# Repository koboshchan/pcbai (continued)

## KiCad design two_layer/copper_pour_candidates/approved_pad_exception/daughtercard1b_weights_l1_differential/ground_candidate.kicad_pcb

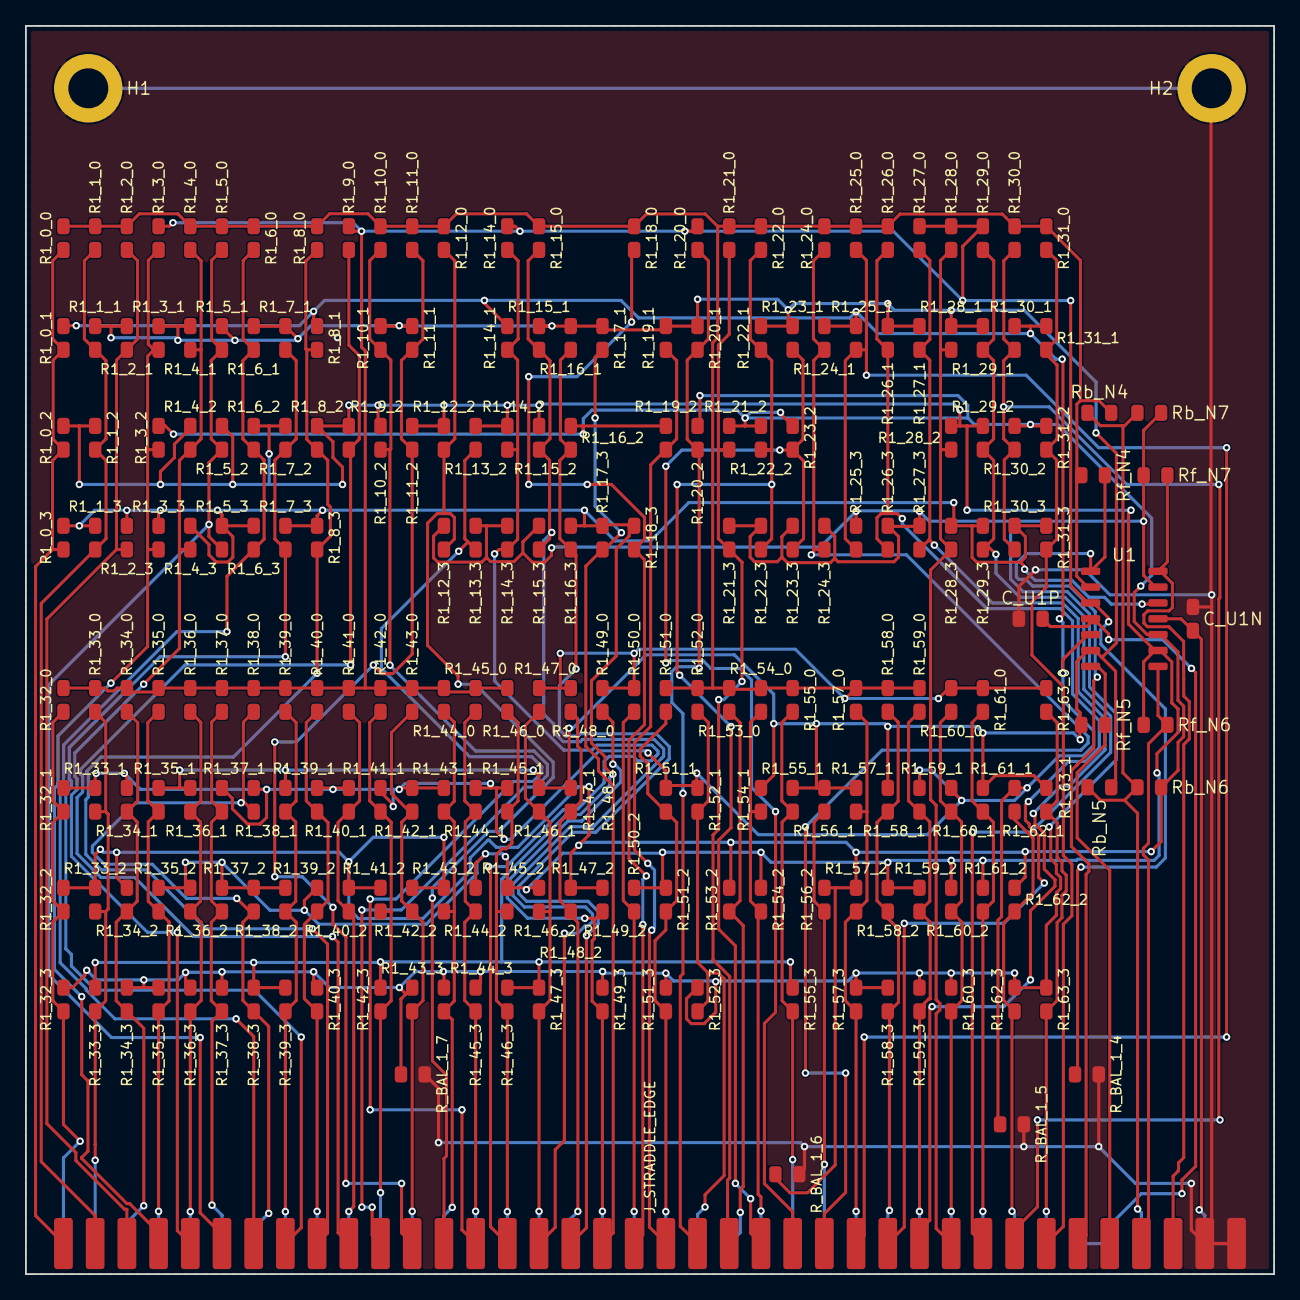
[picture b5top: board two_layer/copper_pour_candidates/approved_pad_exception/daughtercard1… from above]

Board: 2 copper layers, 100.0 x 100.0 mm, 236 parts (0 on the bottom side), 80 nets.

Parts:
C_U1N, C_U1P: 0.1uF; C_0805_2012Metric
H1, H2: MountingHole; MountingHole_3.2mm_M3_Pad
J_STRADDLE_EDGE: PinHeader_2x38_Straddle; PinHeader_2x38_Straddle_P2.54mm
R1_0_0, R1_23_2, R1_40_0, R1_41_0, R1_63_3: 51k; R_0805_2012Metric
R1_0_1, R1_5_3, R1_14_2, R1_38_0, R1_54_0: 130k; R_0805_2012Metric
R1_0_2, R1_0_3, R1_15_3, R1_21_2, R1_22_3, R1_63_1: 75k; R_0805_2012Metric
R1_1_0, R1_2_1, R1_13_2, R1_28_2, R1_35_0, R1_46_0, R1_47_2, R1_49_0, R1_51_1, R1_52_0, R1_57_0, R1_60_0, R1_60_2, R1_62_2: 200k; R_0805_2012Metric
R1_1_1, R1_3_1, R1_4_1, R1_8_3, R1_30_2, R1_36_0, R1_41_1, R1_48_1, R1_55_0: 150k; R_0805_2012Metric
R1_1_2, R1_20_0, R1_45_1, R1_45_2, R1_59_3: 240k; R_0805_2012Metric
R1_1_3, R1_23_1, R1_24_0, R1_32_1, R1_33_1, R1_48_0, R1_55_3: 91k; R_0805_2012Metric
R1_2_0, R1_29_1: 1.3M; R_0805_2012Metric
R1_2_3, R1_3_3, R1_11_0, R1_17_1, R1_18_0, R1_29_2, R1_38_1, R1_38_2, R1_39_0, R1_43_2, R1_59_0, R1_61_1: 330k; R_0805_2012Metric
R1_3_0, R1_11_2, R1_20_1, R1_30_1, R1_35_3: 430k; R_0805_2012Metric
R1_3_2, R1_22_0, R1_33_3, R1_34_2, R1_43_3, R1_46_3, R1_59_2: 680k; R_0805_2012Metric
R1_4_0, R1_9_0, R1_12_2, R1_21_3, R1_37_3, R1_58_1, R1_61_2: 270k; R_0805_2012Metric
R1_4_2, R1_4_3, R1_8_2, R1_24_3, R1_40_2, R1_40_3, R1_43_1: 110k; R_0805_2012Metric
R1_5_0, R1_14_0, R1_16_3, R1_25_3, R1_26_1, R1_42_3, R1_44_2, R1_45_3, R1_48_2, R1_49_2, R1_54_1: 510k; R_0805_2012Metric
R1_5_1, R1_11_1, R1_13_3, R1_24_1, R1_25_0, R1_29_0, R1_35_1, R1_39_1, R1_44_3, R1_45_0, R1_46_2, R1_53_2: 300k; R_0805_2012Metric
R1_5_2, R1_6_3, R1_20_2, R1_31_0, R1_32_0, R1_42_0, R1_42_1, R1_47_1, R1_47_3: 82k; R_0805_2012Metric
R1_6_0, R1_8_0, R1_31_1, R1_43_0: 100k; R_0805_2012Metric
R1_6_1, R1_10_1, R1_15_0, R1_15_1, R1_19_2, R1_27_0, R1_32_3, R1_55_1, R1_56_2, R1_57_3: 160k; R_0805_2012Metric
R1_6_2, R1_22_2: 56k; R_0805_2012Metric
R1_7_1, R1_15_2: 33k; R_0805_2012Metric
R1_7_2: 47k; R_0805_2012Metric
R1_7_3, R1_34_0, R1_35_2, R1_44_0: 390k; R_0805_2012Metric
R1_8_1, R1_22_1, R1_36_1, R1_37_0, R1_41_2, R1_42_2, R1_50_2, R1_54_2: 470k; R_0805_2012Metric
R1_9_2, R1_37_2, R1_62_1: 1M; R_0805_2012Metric
R1_10_0, R1_14_1, R1_58_2: 1.8M; R_0805_2012Metric
R1_10_2, R1_60_1: 1.6M; R_0805_2012Metric
R1_12_0, R1_21_0, R1_46_1, R1_58_3: 820k; R_0805_2012Metric
R1_12_3, R1_34_3, R1_49_3: 1.1M; R_0805_2012Metric
R1_14_3, R1_19_1, R1_25_1, R1_33_0, R1_47_0, R1_53_0: 360k; R_0805_2012Metric
R1_16_1, R1_16_2, R1_28_0, R1_28_3, R1_30_0, R1_38_3: 220k; R_0805_2012Metric
R1_17_3, R1_32_2, R1_36_2, R1_57_2, R1_60_3: 560k; R_0805_2012Metric
R1_18_3: 910k; R_0805_2012Metric
R1_23_3: 24k; R_0805_2012Metric
R1_26_0, R1_36_3, R1_52_1, R1_52_3, R1_59_1: 750k; R_0805_2012Metric
R1_26_3, R1_57_1: 1.5M; R_0805_2012Metric
R1_27_1, R1_33_2, R1_40_1, R1_51_0, R1_61_0: 120k; R_0805_2012Metric
R1_27_3, R1_51_2: 2M; R_0805_2012Metric
R1_28_1, R1_34_1, R1_44_1, R1_50_0, R1_58_0, R1_62_3: 180k; R_0805_2012Metric
R1_29_3, R1_63_0: 62k; R_0805_2012Metric
R1_30_3: 20k; R_0805_2012Metric
R1_31_2, R1_39_2: 68k; R_0805_2012Metric
R1_31_3: 43k; R_0805_2012Metric
R1_37_1: 620k; R_0805_2012Metric
R1_39_3: 27k; R_0805_2012Metric
R1_51_3: 2.2M; R_0805_2012Metric
R1_56_1: 39k; R_0805_2012Metric
R_BAL_1_4: 14.3k; R_0805_2012Metric
R_BAL_1_5: 10k; R_0805_2012Metric
R_BAL_1_6: 13k; R_0805_2012Metric
R_BAL_1_7: 16.2k; R_0805_2012Metric
Rb_N4, Rb_N5: 330k; R_0805_2012Metric
Rb_N6: 1.1M; R_0805_2012Metric
Rb_N7: 390k; R_0805_2012Metric
Rf_N4, Rf_N5, Rf_N6, Rf_N7: 100k; R_0805_2012Metric
U1: TL074; SOIC-14_3.9x8.7mm_P1.27mm

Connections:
+5V_REF: J_STRADDLE_EDGE.B35, Rb_N4.1, Rb_N5.1, Rb_N6.1, Rb_N7.1
+15V: C_U1P.2, J_STRADDLE_EDGE.B33, J_STRADDLE_EDGE.B34, U1.4
-15V: C_U1N.1, J_STRADDLE_EDGE.B37, J_STRADDLE_EDGE.B38, U1.11
GND: C_U1N.2, C_U1P.1, H1.1, H2.1, J_STRADDLE_EDGE.A37, J_STRADDLE_EDGE.A38, R_BAL_1_4.2, R_BAL_1_5.2, R_BAL_1_6.2, R_BAL_1_7.2
INV_N4: R1_0_0.2, R1_1_0.2, R1_2_0.2, R1_4_0.2, R1_5_0.2, R1_6_0.2, R1_8_0.2, R1_10_0.2, R1_11_0.2, R1_12_0.2, R1_15_0.2, R1_18_0.2, R1_21_0.2, R1_22_0.2, R1_24_0.2, R1_25_0.2, R1_26_0.2, R1_30_0.2, R1_31_0.2, R1_47_0.2, R1_48_0.2, R1_49_0.2, R1_50_0.2, R1_51_0.2, R1_52_0.2, R1_53_0.2, R1_54_0.2, R1_55_0.2, R1_57_0.2, R1_58_0.2, R1_59_0.2, R1_60_0.2, R1_61_0.2, R1_63_0.2, Rb_N4.2, Rf_N4.1, U1.2
INV_N5: R1_1_1.2, R1_2_1.2, R1_3_1.2, R1_4_1.2, R1_5_1.2, R1_6_1.2, R1_7_1.2, R1_10_1.2, R1_11_1.2, R1_15_1.2, R1_16_1.2, R1_17_1.2, R1_19_1.2, R1_20_1.2, R1_22_1.2, R1_23_1.2, R1_26_1.2, R1_27_1.2, R1_28_1.2, R1_29_1.2, R1_35_1.2, R1_36_1.2, R1_39_1.2, R1_47_1.2, R1_48_1.2, R1_54_1.2, R1_55_1.2, R1_56_1.2, R1_57_1.2, R1_58_1.2, R1_61_1.2, R1_63_1.2, Rb_N5.2, Rf_N5.1, U1.6
INV_N6: R1_0_2.2, R1_1_2.2, R1_4_2.2, R1_5_2.2, R1_6_2.2, R1_7_2.2, R1_8_2.2, R1_9_2.2, R1_10_2.2, R1_11_2.2, R1_12_2.2, R1_13_2.2, R1_14_2.2, R1_15_2.2, R1_28_2.2, R1_29_2.2, R1_35_2.2, R1_36_2.2, R1_37_2.2, R1_38_2.2, R1_39_2.2, R1_40_2.2, R1_45_2.2, R1_46_2.2, R1_47_2.2, R1_50_2.2, R1_51_2.2, R1_54_2.2, R1_58_2.2, R1_59_2.2, R1_60_2.2, R1_61_2.2, Rf_N6.1, U1.9
INV_N7: R1_12_3.2, R1_13_3.2, R1_14_3.2, R1_15_3.2, R1_21_3.2, R1_22_3.2, R1_23_3.2, R1_24_3.2, R1_25_3.2, R1_26_3.2, R1_27_3.2, R1_32_3.2, R1_34_3.2, R1_35_3.2, R1_36_3.2, R1_37_3.2, R1_40_3.2, R1_43_3.2, R1_44_3.2, R1_45_3.2, R1_49_3.2, R1_51_3.2, R1_52_3.2, R1_57_3.2, R1_58_3.2, R1_59_3.2, R1_60_3.2, R1_62_3.2, R1_63_3.2, R_BAL_1_7.1, Rb_N7.2, Rf_N7.1, U1.13
IN_0: J_STRADDLE_EDGE.A1, R1_0_0.1, R1_0_1.1, R1_0_2.1, R1_0_3.1
IN_1: J_STRADDLE_EDGE.A2, R1_1_0.1, R1_1_1.1, R1_1_2.1, R1_1_3.1
IN_2: J_STRADDLE_EDGE.A3, R1_2_0.1, R1_2_1.1, R1_2_3.1
IN_3: J_STRADDLE_EDGE.A4, R1_3_0.1, R1_3_1.1, R1_3_2.1, R1_3_3.1
IN_4: J_STRADDLE_EDGE.A5, R1_4_0.1, R1_4_1.1, R1_4_2.1, R1_4_3.1
IN_5: J_STRADDLE_EDGE.A6, R1_5_0.1, R1_5_1.1, R1_5_2.1, R1_5_3.1
IN_6: J_STRADDLE_EDGE.A7, R1_6_0.1, R1_6_1.1, R1_6_2.1, R1_6_3.1
IN_7: J_STRADDLE_EDGE.A8, R1_7_1.1, R1_7_2.1, R1_7_3.1
IN_8: J_STRADDLE_EDGE.A9, R1_8_0.1, R1_8_1.1, R1_8_2.1, R1_8_3.1
IN_9: J_STRADDLE_EDGE.A10, R1_9_0.1, R1_9_2.1
IN_10: J_STRADDLE_EDGE.A11, R1_10_0.1, R1_10_1.1, R1_10_2.1
IN_11: J_STRADDLE_EDGE.A12, R1_11_0.1, R1_11_1.1, R1_11_2.1
IN_12: J_STRADDLE_EDGE.A13, R1_12_0.1, R1_12_2.1, R1_12_3.1
IN_13: J_STRADDLE_EDGE.A14, R1_13_2.1, R1_13_3.1
IN_14: J_STRADDLE_EDGE.A15, R1_14_0.1, R1_14_1.1, R1_14_2.1, R1_14_3.1
IN_15: J_STRADDLE_EDGE.A16, R1_15_0.1, R1_15_1.1, R1_15_2.1, R1_15_3.1
IN_16: J_STRADDLE_EDGE.A17, R1_16_1.1, R1_16_2.1, R1_16_3.1
IN_17: J_STRADDLE_EDGE.A18, R1_17_1.1, R1_17_3.1
IN_18: J_STRADDLE_EDGE.A19, R1_18_0.1, R1_18_3.1
IN_19: J_STRADDLE_EDGE.A20, R1_19_1.1, R1_19_2.1
IN_20: J_STRADDLE_EDGE.A21, R1_20_0.1, R1_20_1.1, R1_20_2.1
IN_21: J_STRADDLE_EDGE.A22, R1_21_0.1, R1_21_2.1, R1_21_3.1
IN_22: J_STRADDLE_EDGE.A23, R1_22_0.1, R1_22_1.1, R1_22_2.1, R1_22_3.1
IN_23: J_STRADDLE_EDGE.A24, R1_23_1.1, R1_23_2.1, R1_23_3.1
IN_24: J_STRADDLE_EDGE.A25, R1_24_0.1, R1_24_1.1, R1_24_3.1
IN_25: J_STRADDLE_EDGE.A26, R1_25_0.1, R1_25_1.1, R1_25_3.1
IN_26: J_STRADDLE_EDGE.A27, R1_26_0.1, R1_26_1.1, R1_26_3.1
IN_27: J_STRADDLE_EDGE.A28, R1_27_0.1, R1_27_1.1, R1_27_3.1
IN_28: J_STRADDLE_EDGE.A29, R1_28_0.1, R1_28_1.1, R1_28_2.1, R1_28_3.1
IN_29: J_STRADDLE_EDGE.A30, R1_29_0.1, R1_29_1.1, R1_29_2.1, R1_29_3.1
IN_30: J_STRADDLE_EDGE.A31, R1_30_0.1, R1_30_1.1, R1_30_2.1, R1_30_3.1
IN_31: J_STRADDLE_EDGE.A32, R1_31_0.1, R1_31_1.1, R1_31_2.1, R1_31_3.1
IN_32: J_STRADDLE_EDGE.B1, R1_32_0.1, R1_32_1.1, R1_32_2.1, R1_32_3.1
IN_33: J_STRADDLE_EDGE.B2, R1_33_0.1, R1_33_1.1, R1_33_2.1, R1_33_3.1
IN_34: J_STRADDLE_EDGE.B3, R1_34_0.1, R1_34_1.1, R1_34_2.1, R1_34_3.1
IN_35: J_STRADDLE_EDGE.B4, R1_35_0.1, R1_35_1.1, R1_35_2.1, R1_35_3.1
IN_36: J_STRADDLE_EDGE.B5, R1_36_0.1, R1_36_1.1, R1_36_2.1, R1_36_3.1
IN_37: J_STRADDLE_EDGE.B6, R1_37_0.1, R1_37_1.1, R1_37_2.1, R1_37_3.1
IN_38: J_STRADDLE_EDGE.B7, R1_38_0.1, R1_38_1.1, R1_38_2.1, R1_38_3.1
IN_39: J_STRADDLE_EDGE.B8, R1_39_0.1, R1_39_1.1, R1_39_2.1, R1_39_3.1
IN_40: J_STRADDLE_EDGE.B9, R1_40_0.1, R1_40_1.1, R1_40_2.1, R1_40_3.1
IN_41: J_STRADDLE_EDGE.B10, R1_41_0.1, R1_41_1.1, R1_41_2.1
IN_42: J_STRADDLE_EDGE.B11, R1_42_0.1, R1_42_1.1, R1_42_2.1, R1_42_3.1
IN_43: J_STRADDLE_EDGE.B12, R1_43_0.1, R1_43_1.1, R1_43_2.1, R1_43_3.1
IN_44: J_STRADDLE_EDGE.B13, R1_44_0.1, R1_44_1.1, R1_44_2.1, R1_44_3.1
IN_45: J_STRADDLE_EDGE.B14, R1_45_0.1, R1_45_1.1, R1_45_2.1, R1_45_3.1
IN_46: J_STRADDLE_EDGE.B15, R1_46_0.1, R1_46_1.1, R1_46_2.1, R1_46_3.1
IN_47: J_STRADDLE_EDGE.B16, R1_47_0.1, R1_47_1.1, R1_47_2.1, R1_47_3.1
IN_48: J_STRADDLE_EDGE.B17, R1_48_0.1, R1_48_1.1, R1_48_2.1
IN_49: J_STRADDLE_EDGE.B18, R1_49_0.1, R1_49_2.1, R1_49_3.1
IN_50: J_STRADDLE_EDGE.B19, R1_50_0.1, R1_50_2.1
IN_51: J_STRADDLE_EDGE.B20, R1_51_0.1, R1_51_1.1, R1_51_2.1, R1_51_3.1
IN_52: J_STRADDLE_EDGE.B21, R1_52_0.1, R1_52_1.1, R1_52_3.1
IN_53: J_STRADDLE_EDGE.B22, R1_53_0.1, R1_53_2.1
IN_54: J_STRADDLE_EDGE.B23, R1_54_0.1, R1_54_1.1, R1_54_2.1
IN_55: J_STRADDLE_EDGE.B24, R1_55_0.1, R1_55_1.1, R1_55_3.1
IN_56: J_STRADDLE_EDGE.B25, R1_56_1.1, R1_56_2.1
IN_57: J_STRADDLE_EDGE.B26, R1_57_0.1, R1_57_1.1, R1_57_2.1, R1_57_3.1
IN_58: J_STRADDLE_EDGE.B27, R1_58_0.1, R1_58_1.1, R1_58_2.1, R1_58_3.1
IN_59: J_STRADDLE_EDGE.B28, R1_59_0.1, R1_59_1.1, R1_59_2.1, R1_59_3.1
IN_60: J_STRADDLE_EDGE.B29, R1_60_0.1, R1_60_1.1, R1_60_2.1, R1_60_3.1
IN_61: J_STRADDLE_EDGE.B30, R1_61_0.1, R1_61_1.1, R1_61_2.1
IN_62: J_STRADDLE_EDGE.B31, R1_62_1.1, R1_62_2.1, R1_62_3.1
IN_63: J_STRADDLE_EDGE.B32, R1_63_0.1, R1_63_1.1, R1_63_3.1
POS_N4: R1_3_0.2, R1_9_0.2, R1_14_0.2, R1_20_0.2, R1_27_0.2, R1_28_0.2, R1_29_0.2, R1_32_0.2, R1_33_0.2, R1_34_0.2, R1_35_0.2, R1_36_0.2, R1_37_0.2, R1_38_0.2, R1_39_0.2, R1_40_0.2, R1_41_0.2, R1_42_0.2, R1_43_0.2, R1_44_0.2, R1_45_0.2, R1_46_0.2, R_BAL_1_4.1, U1.3
POS_N5: R1_0_1.2, R1_8_1.2, R1_14_1.2, R1_24_1.2, R1_25_1.2, R1_30_1.2, R1_31_1.2, R1_32_1.2, R1_33_1.2, R1_34_1.2, R1_37_1.2, R1_38_1.2, R1_40_1.2, R1_41_1.2, R1_42_1.2, R1_43_1.2, R1_44_1.2, R1_45_1.2, R1_46_1.2, R1_51_1.2, R1_52_1.2, R1_59_1.2, R1_60_1.2, R1_62_1.2, R_BAL_1_5.1, U1.5
POS_N6: R1_3_2.2, R1_16_2.2, R1_19_2.2, R1_20_2.2, R1_21_2.2, R1_22_2.2, R1_23_2.2, R1_30_2.2, R1_31_2.2, R1_32_2.2, R1_33_2.2, R1_34_2.2, R1_41_2.2, R1_42_2.2, R1_43_2.2, R1_44_2.2, R1_48_2.2, R1_49_2.2, R1_53_2.2, R1_56_2.2, R1_57_2.2, R1_62_2.2, R_BAL_1_6.1, Rb_N6.2, U1.10
POS_N7: R1_0_3.2, R1_1_3.2, R1_2_3.2, R1_3_3.2, R1_4_3.2, R1_5_3.2, R1_6_3.2, R1_7_3.2, R1_8_3.2, R1_16_3.2, R1_17_3.2, R1_18_3.2, R1_28_3.2, R1_29_3.2, R1_30_3.2, R1_31_3.2, R1_33_3.2, R1_38_3.2, R1_39_3.2, R1_42_3.2, R1_46_3.2, R1_47_3.2, R1_55_3.2, U1.12
V_SUM_4: J_STRADDLE_EDGE.A33, Rf_N4.2, U1.1
V_SUM_5: J_STRADDLE_EDGE.A34, Rf_N5.2, U1.7
V_SUM_6: J_STRADDLE_EDGE.A35, Rf_N6.2, U1.8
V_SUM_7: J_STRADDLE_EDGE.A36, Rf_N7.2, U1.14

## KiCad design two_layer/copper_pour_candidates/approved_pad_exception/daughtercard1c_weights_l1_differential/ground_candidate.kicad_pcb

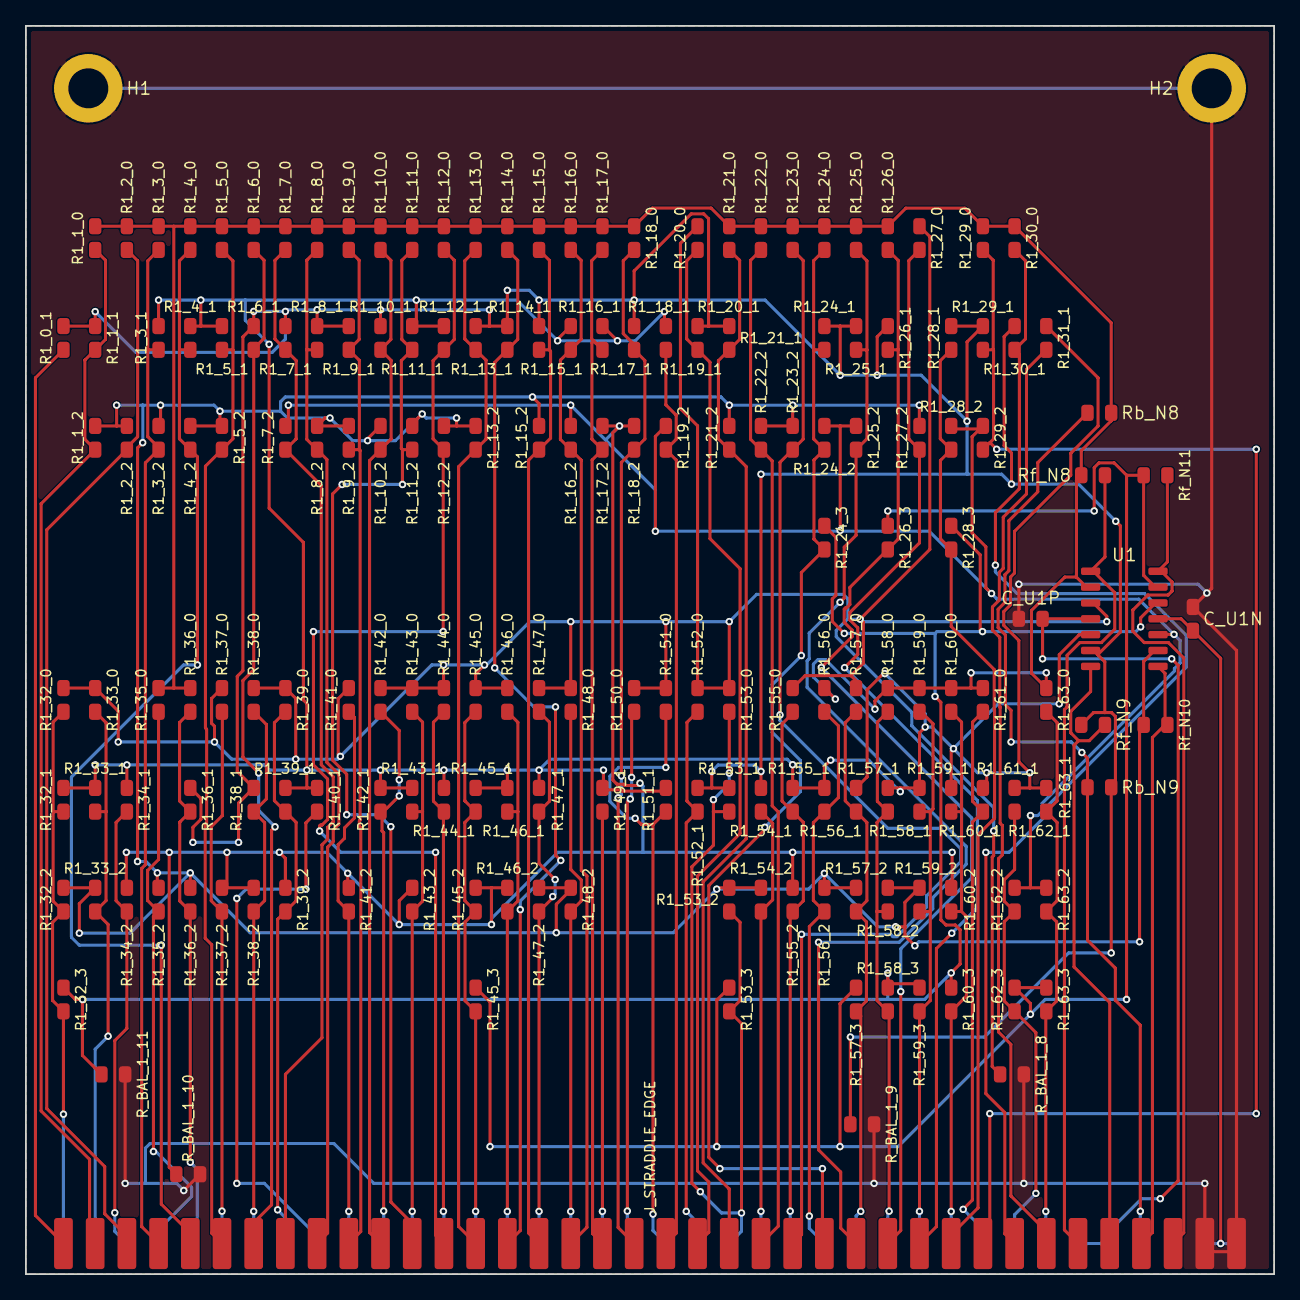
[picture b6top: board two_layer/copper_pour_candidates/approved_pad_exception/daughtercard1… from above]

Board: 2 copper layers, 100.0 x 100.0 mm, 187 parts (0 on the bottom side), 80 nets.

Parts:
C_U1N, C_U1P: 0.1uF; C_0805_2012Metric
H1, H2: MountingHole; MountingHole_3.2mm_M3_Pad
J_STRADDLE_EDGE: PinHeader_2x38_Straddle; PinHeader_2x38_Straddle_P2.54mm
R1_0_1: 51k; R_0805_2012Metric
R1_1_0, R1_4_0, R1_11_1, R1_13_1, R1_23_2, R1_28_3, R1_43_1, R1_45_0: 180k; R_0805_2012Metric
R1_1_1: 33k; R_0805_2012Metric
R1_1_2, R1_4_1: 43k; R_0805_2012Metric
R1_2_0, R1_22_2, R1_26_1, R1_28_2, R1_33_1, R1_37_0, R1_37_2, R1_39_2, R1_44_0, R1_44_1, R1_45_1, R1_46_1, R1_48_2, R1_49_1, R1_59_2: 270k; R_0805_2012Metric
R1_2_2, R1_3_1, R1_18_2, R1_56_0: 62k; R_0805_2012Metric
R1_3_0, R1_36_2: 1M; R_0805_2012Metric
R1_3_2, R1_18_0, R1_22_0: 120k; R_0805_2012Metric
R1_4_2, R1_14_1, R1_17_0, R1_18_1, R1_34_1, R1_63_1: 160k; R_0805_2012Metric
R1_5_0, R1_9_1, R1_11_0, R1_47_2, R1_59_0: 360k; R_0805_2012Metric
R1_5_1, R1_8_0, R1_19_2: 75k; R_0805_2012Metric
R1_5_2, R1_10_1, R1_21_1, R1_28_1, R1_39_0, R1_41_0, R1_45_3, R1_63_0: 240k; R_0805_2012Metric
R1_6_0, R1_12_2, R1_19_1, R1_33_2, R1_57_2: 330k; R_0805_2012Metric
R1_6_1, R1_11_2, R1_15_1, R1_16_0, R1_32_0, R1_56_1, R1_60_3, R1_62_1: 110k; R_0805_2012Metric
R1_7_0, R1_16_2, R1_17_2, R1_32_2: 47k; R_0805_2012Metric
R1_7_1, R1_8_2, R1_47_1: 39k; R_0805_2012Metric
R1_7_2: 27k; R_0805_2012Metric
R1_8_1, R1_10_2, R1_16_1, R1_32_1, R1_38_0: 91k; R_0805_2012Metric
R1_9_0, R1_52_0, R1_53_0, R1_53_2: 620k; R_0805_2012Metric
R1_9_2, R1_56_2: 100k; R_0805_2012Metric
R1_10_0, R1_13_0, R1_17_1, R1_50_0, R1_51_0, R1_58_1, R1_58_2: 220k; R_0805_2012Metric
R1_12_0, R1_33_0, R1_46_2: 430k; R_0805_2012Metric
R1_12_1, R1_42_1, R1_43_0, R1_53_3, R1_57_0, R1_59_3, R1_61_0: 300k; R_0805_2012Metric
R1_13_2, R1_26_0, R1_43_2, R1_47_0, R1_58_3, R1_63_3: 560k; R_0805_2012Metric
R1_14_0, R1_38_1, R1_38_2, R1_60_0: 510k; R_0805_2012Metric
R1_15_0, R1_40_1, R1_61_1: 68k; R_0805_2012Metric
R1_15_2: 82k; R_0805_2012Metric
R1_20_0, R1_25_0, R1_27_0, R1_42_0, R1_60_1: 470k; R_0805_2012Metric
R1_20_1, R1_35_0, R1_41_2, R1_59_1: 390k; R_0805_2012Metric
R1_21_0, R1_23_0, R1_24_1, R1_30_1, R1_39_1, R1_57_1: 130k; R_0805_2012Metric
R1_21_2, R1_32_3, R1_34_2: 910k; R_0805_2012Metric
R1_24_0, R1_30_0, R1_54_2, R1_62_2: 200k; R_0805_2012Metric
R1_24_2, R1_55_1: 56k; R_0805_2012Metric
R1_24_3, R1_25_2, R1_35_2, R1_36_0, R1_51_1, R1_52_1: 750k; R_0805_2012Metric
R1_25_1, R1_29_1, R1_46_0, R1_57_3, R1_62_3: 150k; R_0805_2012Metric
R1_26_3: 2.2M; R_0805_2012Metric
R1_27_2, R1_53_1, R1_54_1, R1_60_2: 820k; R_0805_2012Metric
R1_29_0, R1_55_0: 1.2M; R_0805_2012Metric
R1_29_2, R1_55_2: 1.3M; R_0805_2012Metric
R1_31_1: 3M; R_0805_2012Metric
R1_36_1, R1_48_0: 1.1M; R_0805_2012Metric
R1_45_2: 2M; R_0805_2012Metric
R1_58_0: 680k; R_0805_2012Metric
R1_63_2: 36k; R_0805_2012Metric
R_BAL_1_8: 8.66k; R_0805_2012Metric
R_BAL_1_9: 18.2k; R_0805_2012Metric
R_BAL_1_10: 35.7k; R_0805_2012Metric
R_BAL_1_11: 90.9k; R_0805_2012Metric
Rb_N8: 820k; R_0805_2012Metric
Rb_N9: 270k; R_0805_2012Metric
Rf_N8, Rf_N9, Rf_N10, Rf_N11: 100k; R_0805_2012Metric
U1: TL074; SOIC-14_3.9x8.7mm_P1.27mm

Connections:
+5V_REF: J_STRADDLE_EDGE.B35, Rb_N8.1, Rb_N9.1
+15V: C_U1P.2, J_STRADDLE_EDGE.B33, J_STRADDLE_EDGE.B34, U1.4
-15V: C_U1N.1, J_STRADDLE_EDGE.B37, J_STRADDLE_EDGE.B38, U1.11
GND: C_U1N.2, C_U1P.1, H1.1, H2.1, J_STRADDLE_EDGE.A37, J_STRADDLE_EDGE.A38, R_BAL_1_8.2, R_BAL_1_9.2, R_BAL_1_10.2, R_BAL_1_11.2
INV_N8: R1_1_0.2, R1_2_0.2, R1_3_0.2, R1_4_0.2, R1_5_0.2, R1_6_0.2, R1_7_0.2, R1_8_0.2, R1_9_0.2, R1_10_0.2, R1_11_0.2, R1_12_0.2, R1_13_0.2, R1_14_0.2, R1_15_0.2, R1_16_0.2, R1_17_0.2, R1_18_0.2, R1_21_0.2, R1_22_0.2, R1_23_0.2, R1_24_0.2, R1_25_0.2, R1_26_0.2, R1_29_0.2, R1_30_0.2, R1_35_0.2, R1_36_0.2, R1_56_0.2, R1_58_0.2, R1_59_0.2, R1_60_0.2, R1_61_0.2, R1_63_0.2, Rb_N8.2, Rf_N8.1, U1.2
INV_N9: R1_0_1.2, R1_1_1.2, R1_6_1.2, R1_7_1.2, R1_8_1.2, R1_9_1.2, R1_10_1.2, R1_13_1.2, R1_14_1.2, R1_15_1.2, R1_18_1.2, R1_20_1.2, R1_21_1.2, R1_24_1.2, R1_25_1.2, R1_26_1.2, R1_28_1.2, R1_29_1.2, R1_30_1.2, R1_36_1.2, R1_38_1.2, R1_52_1.2, R1_53_1.2, R1_54_1.2, R_BAL_1_9.1, Rb_N9.2, Rf_N9.1, U1.6
INV_N10: R1_1_2.2, R1_2_2.2, R1_3_2.2, R1_4_2.2, R1_5_2.2, R1_8_2.2, R1_9_2.2, R1_10_2.2, R1_11_2.2, R1_12_2.2, R1_13_2.2, R1_15_2.2, R1_21_2.2, R1_22_2.2, R1_23_2.2, R1_27_2.2, R1_32_2.2, R1_33_2.2, R1_35_2.2, R1_36_2.2, R1_47_2.2, R1_48_2.2, R1_53_2.2, R1_54_2.2, R1_56_2.2, R1_57_2.2, R1_58_2.2, R1_59_2.2, Rf_N10.1, U1.9
INV_N11: R1_26_3.2, R1_45_3.2, R1_53_3.2, R1_57_3.2, R1_62_3.2, R1_63_3.2, Rf_N11.1, U1.13
IN_0: J_STRADDLE_EDGE.A1, R1_0_1.1
IN_1: J_STRADDLE_EDGE.A2, R1_1_0.1, R1_1_1.1, R1_1_2.1
IN_2: J_STRADDLE_EDGE.A3, R1_2_0.1, R1_2_2.1
IN_3: J_STRADDLE_EDGE.A4, R1_3_0.1, R1_3_1.1, R1_3_2.1
IN_4: J_STRADDLE_EDGE.A5, R1_4_0.1, R1_4_1.1, R1_4_2.1
IN_5: J_STRADDLE_EDGE.A6, R1_5_0.1, R1_5_1.1, R1_5_2.1
IN_6: J_STRADDLE_EDGE.A7, R1_6_0.1, R1_6_1.1
IN_7: J_STRADDLE_EDGE.A8, R1_7_0.1, R1_7_1.1, R1_7_2.1
IN_8: J_STRADDLE_EDGE.A9, R1_8_0.1, R1_8_1.1, R1_8_2.1
IN_9: J_STRADDLE_EDGE.A10, R1_9_0.1, R1_9_1.1, R1_9_2.1
IN_10: J_STRADDLE_EDGE.A11, R1_10_0.1, R1_10_1.1, R1_10_2.1
IN_11: J_STRADDLE_EDGE.A12, R1_11_0.1, R1_11_1.1, R1_11_2.1
IN_12: J_STRADDLE_EDGE.A13, R1_12_0.1, R1_12_1.1, R1_12_2.1
IN_13: J_STRADDLE_EDGE.A14, R1_13_0.1, R1_13_1.1, R1_13_2.1
IN_14: J_STRADDLE_EDGE.A15, R1_14_0.1, R1_14_1.1
IN_15: J_STRADDLE_EDGE.A16, R1_15_0.1, R1_15_1.1, R1_15_2.1
IN_16: J_STRADDLE_EDGE.A17, R1_16_0.1, R1_16_1.1, R1_16_2.1
IN_17: J_STRADDLE_EDGE.A18, R1_17_0.1, R1_17_1.1, R1_17_2.1
IN_18: J_STRADDLE_EDGE.A19, R1_18_0.1, R1_18_1.1, R1_18_2.1
IN_19: J_STRADDLE_EDGE.A20, R1_19_1.1, R1_19_2.1
IN_20: J_STRADDLE_EDGE.A21, R1_20_0.1, R1_20_1.1
IN_21: J_STRADDLE_EDGE.A22, R1_21_0.1, R1_21_1.1, R1_21_2.1
IN_22: J_STRADDLE_EDGE.A23, R1_22_0.1, R1_22_2.1
IN_23: J_STRADDLE_EDGE.A24, R1_23_0.1, R1_23_2.1
IN_24: J_STRADDLE_EDGE.A25, R1_24_0.1, R1_24_1.1, R1_24_2.1, R1_24_3.1
IN_25: J_STRADDLE_EDGE.A26, R1_25_0.1, R1_25_1.1, R1_25_2.1
IN_26: J_STRADDLE_EDGE.A27, R1_26_0.1, R1_26_1.1, R1_26_3.1
IN_27: J_STRADDLE_EDGE.A28, R1_27_0.1, R1_27_2.1
IN_28: J_STRADDLE_EDGE.A29, R1_28_1.1, R1_28_2.1, R1_28_3.1
IN_29: J_STRADDLE_EDGE.A30, R1_29_0.1, R1_29_1.1, R1_29_2.1
IN_30: J_STRADDLE_EDGE.A31, R1_30_0.1, R1_30_1.1
IN_31: J_STRADDLE_EDGE.A32, R1_31_1.1
IN_32: J_STRADDLE_EDGE.B1, R1_32_0.1, R1_32_1.1, R1_32_2.1, R1_32_3.1
IN_33: J_STRADDLE_EDGE.B2, R1_33_0.1, R1_33_1.1, R1_33_2.1
IN_34: J_STRADDLE_EDGE.B3, R1_34_1.1, R1_34_2.1
IN_35: J_STRADDLE_EDGE.B4, R1_35_0.1, R1_35_2.1
IN_36: J_STRADDLE_EDGE.B5, R1_36_0.1, R1_36_1.1, R1_36_2.1
IN_37: J_STRADDLE_EDGE.B6, R1_37_0.1, R1_37_2.1
IN_38: J_STRADDLE_EDGE.B7, R1_38_0.1, R1_38_1.1, R1_38_2.1
IN_39: J_STRADDLE_EDGE.B8, R1_39_0.1, R1_39_1.1, R1_39_2.1
IN_40: J_STRADDLE_EDGE.B9, R1_40_1.1
IN_41: J_STRADDLE_EDGE.B10, R1_41_0.1, R1_41_2.1
IN_42: J_STRADDLE_EDGE.B11, R1_42_0.1, R1_42_1.1
IN_43: J_STRADDLE_EDGE.B12, R1_43_0.1, R1_43_1.1, R1_43_2.1
IN_44: J_STRADDLE_EDGE.B13, R1_44_0.1, R1_44_1.1
IN_45: J_STRADDLE_EDGE.B14, R1_45_0.1, R1_45_1.1, R1_45_2.1, R1_45_3.1
IN_46: J_STRADDLE_EDGE.B15, R1_46_0.1, R1_46_1.1, R1_46_2.1
IN_47: J_STRADDLE_EDGE.B16, R1_47_0.1, R1_47_1.1, R1_47_2.1
IN_48: J_STRADDLE_EDGE.B17, R1_48_0.1, R1_48_2.1
IN_49: J_STRADDLE_EDGE.B18, R1_49_1.1
IN_50: J_STRADDLE_EDGE.B19, R1_50_0.1
IN_51: J_STRADDLE_EDGE.B20, R1_51_0.1, R1_51_1.1
IN_52: J_STRADDLE_EDGE.B21, R1_52_0.1, R1_52_1.1
IN_53: J_STRADDLE_EDGE.B22, R1_53_0.1, R1_53_1.1, R1_53_2.1, R1_53_3.1
IN_54: J_STRADDLE_EDGE.B23, R1_54_1.1, R1_54_2.1
IN_55: J_STRADDLE_EDGE.B24, R1_55_0.1, R1_55_1.1, R1_55_2.1
IN_56: J_STRADDLE_EDGE.B25, R1_56_0.1, R1_56_1.1, R1_56_2.1
IN_57: J_STRADDLE_EDGE.B26, R1_57_0.1, R1_57_1.1, R1_57_2.1, R1_57_3.1
IN_58: J_STRADDLE_EDGE.B27, R1_58_0.1, R1_58_1.1, R1_58_2.1, R1_58_3.1
IN_59: J_STRADDLE_EDGE.B28, R1_59_0.1, R1_59_1.1, R1_59_2.1, R1_59_3.1
IN_60: J_STRADDLE_EDGE.B29, R1_60_0.1, R1_60_1.1, R1_60_2.1, R1_60_3.1
IN_61: J_STRADDLE_EDGE.B30, R1_61_0.1, R1_61_1.1
IN_62: J_STRADDLE_EDGE.B31, R1_62_1.1, R1_62_2.1, R1_62_3.1
IN_63: J_STRADDLE_EDGE.B32, R1_63_0.1, R1_63_1.1, R1_63_2.1, R1_63_3.1
POS_N8: R1_20_0.2, R1_27_0.2, R1_32_0.2, R1_33_0.2, R1_37_0.2, R1_38_0.2, R1_39_0.2, R1_41_0.2, R1_42_0.2, R1_43_0.2, R1_44_0.2, R1_45_0.2, R1_46_0.2, R1_47_0.2, R1_48_0.2, R1_50_0.2, R1_51_0.2, R1_52_0.2, R1_53_0.2, R1_55_0.2, R1_57_0.2, R_BAL_1_8.1, U1.3
POS_N9: R1_3_1.2, R1_4_1.2, R1_5_1.2, R1_11_1.2, R1_12_1.2, R1_16_1.2, R1_17_1.2, R1_19_1.2, R1_31_1.2, R1_32_1.2, R1_33_1.2, R1_34_1.2, R1_39_1.2, R1_40_1.2, R1_42_1.2, R1_43_1.2, R1_44_1.2, R1_45_1.2, R1_46_1.2, R1_47_1.2, R1_49_1.2, R1_51_1.2, R1_55_1.2, R1_56_1.2, R1_57_1.2, R1_58_1.2, R1_59_1.2, R1_60_1.2, R1_61_1.2, R1_62_1.2, R1_63_1.2, U1.5
POS_N10: R1_7_2.2, R1_16_2.2, R1_17_2.2, R1_18_2.2, R1_19_2.2, R1_24_2.2, R1_25_2.2, R1_28_2.2, R1_29_2.2, R1_34_2.2, R1_37_2.2, R1_38_2.2, R1_39_2.2, R1_41_2.2, R1_43_2.2, R1_45_2.2, R1_46_2.2, R1_55_2.2, R1_60_2.2, R1_62_2.2, R1_63_2.2, R_BAL_1_10.1, U1.10
POS_N11: R1_24_3.2, R1_28_3.2, R1_32_3.2, R1_58_3.2, R1_59_3.2, R1_60_3.2, R_BAL_1_11.1, U1.12
V_SUM_8: J_STRADDLE_EDGE.A33, Rf_N8.2, U1.1
V_SUM_9: J_STRADDLE_EDGE.A34, Rf_N9.2, U1.7
V_SUM_10: J_STRADDLE_EDGE.A35, Rf_N10.2, U1.8
V_SUM_11: J_STRADDLE_EDGE.A36, Rf_N11.2, U1.14

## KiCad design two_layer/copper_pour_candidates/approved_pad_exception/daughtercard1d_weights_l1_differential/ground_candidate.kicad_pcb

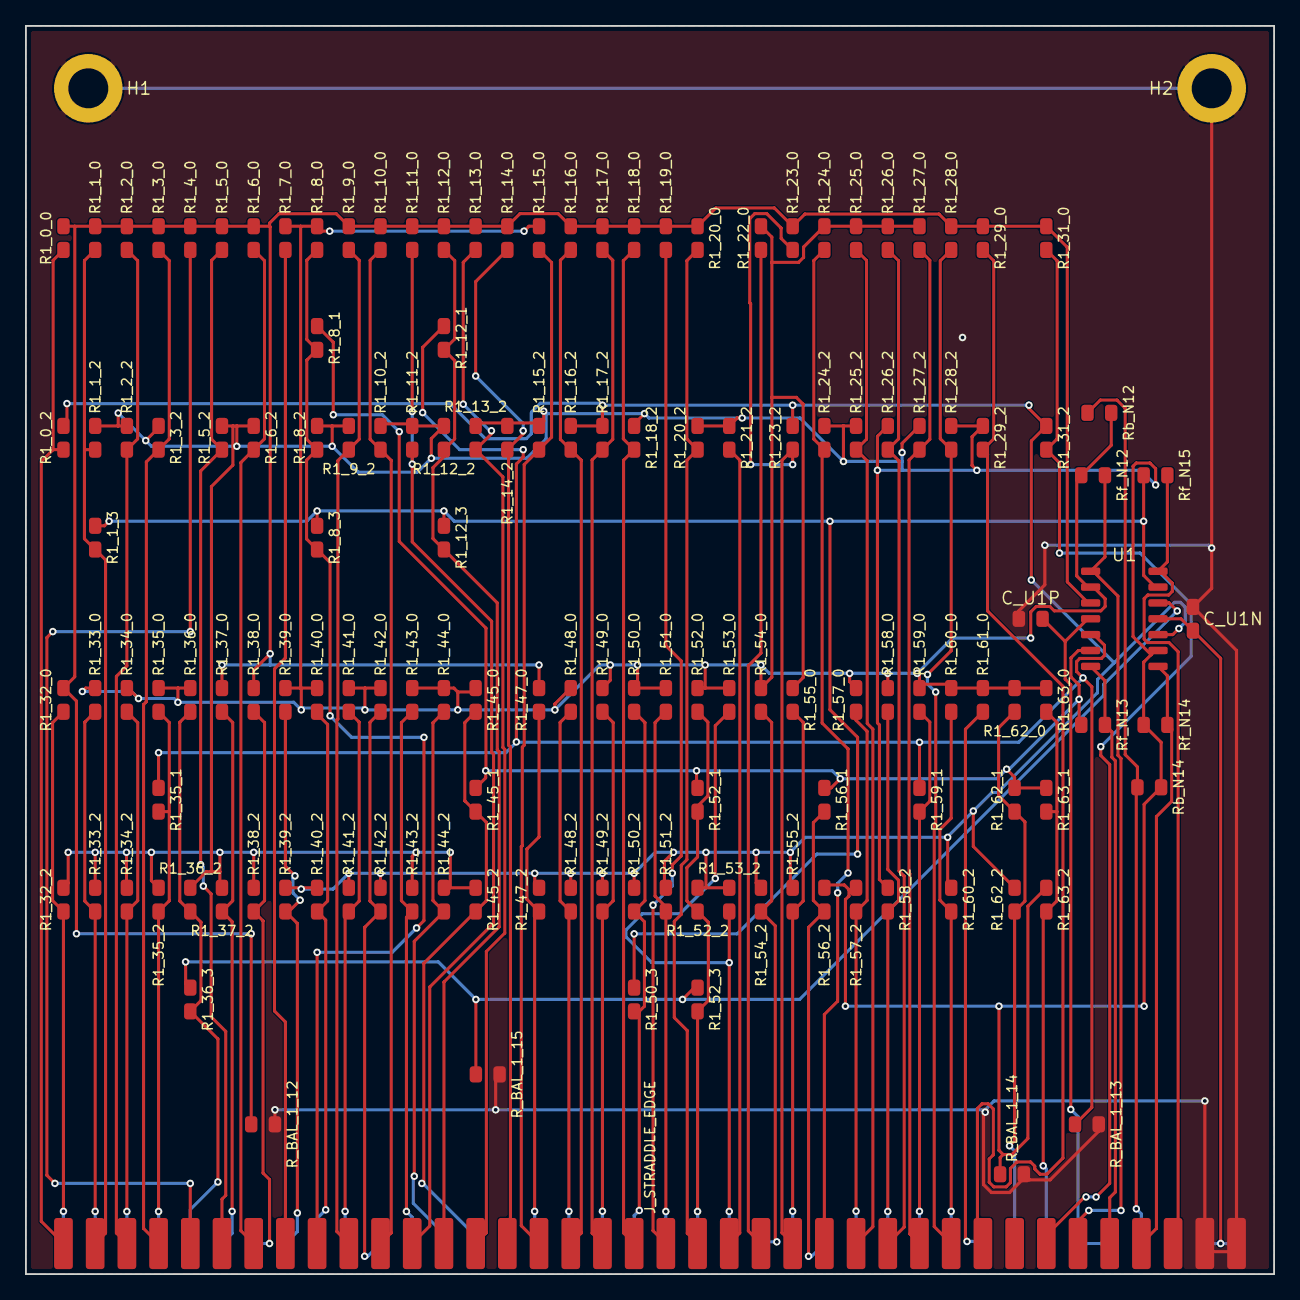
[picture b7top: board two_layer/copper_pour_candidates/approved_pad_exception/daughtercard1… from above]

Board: 2 copper layers, 100.0 x 100.0 mm, 147 parts (0 on the bottom side), 78 nets.

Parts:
C_U1N, C_U1P: 0.1uF; C_0805_2012Metric
H1, H2: MountingHole; MountingHole_3.2mm_M3_Pad
J_STRADDLE_EDGE: PinHeader_2x38_Straddle; PinHeader_2x38_Straddle_P2.54mm
R1_0_0: 43k; R_0805_2012Metric
R1_0_2, R1_31_2: 39k; R_0805_2012Metric
R1_1_0, R1_3_0, R1_5_2, R1_51_0, R1_56_1, R1_62_0, R1_62_1: 200k; R_0805_2012Metric
R1_1_2, R1_39_2: 91k; R_0805_2012Metric
R1_1_3, R1_12_3, R1_15_0, R1_17_2, R1_24_0, R1_34_0, R1_38_0: 220k; R_0805_2012Metric
R1_2_0, R1_13_0, R1_25_0, R1_63_1: 390k; R_0805_2012Metric
R1_2_2, R1_47_2, R1_55_0, R1_63_0: 100k; R_0805_2012Metric
R1_3_2, R1_24_2, R1_26_2, R1_48_2, R1_52_0, R1_59_0: 150k; R_0805_2012Metric
R1_4_0, R1_10_0, R1_14_2, R1_34_2, R1_50_0: 300k; R_0805_2012Metric
R1_5_0, R1_7_0, R1_9_2, R1_11_0, R1_13_2, R1_32_0, R1_37_2, R1_42_2, R1_49_0: 270k; R_0805_2012Metric
R1_6_0, R1_12_1, R1_18_2: 750k; R_0805_2012Metric
R1_6_2, R1_20_0: 110k; R_0805_2012Metric
R1_8_0, R1_25_2, R1_33_2, R1_36_2, R1_36_3, R1_41_2, R1_52_3, R1_57_0, R1_58_0, R1_61_0, R1_63_2: 160k; R_0805_2012Metric
R1_8_1, R1_28_2, R1_37_0, R1_40_0, R1_44_0, R1_45_0, R1_58_2: 430k; R_0805_2012Metric
R1_8_2, R1_56_2: 36k; R_0805_2012Metric
R1_8_3, R1_35_0, R1_41_0, R1_45_1, R1_59_1, R1_60_2: 180k; R_0805_2012Metric
R1_9_0, R1_43_2: 910k; R_0805_2012Metric
R1_10_2, R1_12_0, R1_26_0, R1_27_0, R1_35_2: 360k; R_0805_2012Metric
R1_11_2, R1_14_0, R1_16_0, R1_29_0, R1_33_0, R1_36_0, R1_52_1, R1_62_2: 330k; R_0805_2012Metric
R1_12_2: 1.1M; R_0805_2012Metric
R1_15_2, R1_47_0, R1_53_0: 120k; R_0805_2012Metric
R1_16_2, R1_52_2, R1_54_0: 75k; R_0805_2012Metric
R1_17_0, R1_23_0: 510k; R_0805_2012Metric
R1_18_0: 1M; R_0805_2012Metric
R1_19_0, R1_35_1, R1_39_0, R1_48_0: 130k; R_0805_2012Metric
R1_20_2: 820k; R_0805_2012Metric
R1_21_2: 2M; R_0805_2012Metric
R1_22_0: 1.5M; R_0805_2012Metric
R1_23_2: 51k; R_0805_2012Metric
R1_27_2, R1_45_2: 1.3M; R_0805_2012Metric
R1_28_0, R1_44_2: 560k; R_0805_2012Metric
R1_29_2, R1_32_2, R1_42_0: 470k; R_0805_2012Metric
R1_31_0, R1_38_2, R1_50_3, R1_55_2: 240k; R_0805_2012Metric
R1_40_2: 680k; R_0805_2012Metric
R1_43_0: 2.2M; R_0805_2012Metric
R1_49_2, R1_54_2: 68k; R_0805_2012Metric
R1_50_2, R1_57_2: 82k; R_0805_2012Metric
R1_51_2, R1_53_2: 62k; R_0805_2012Metric
R1_60_0: 1.2M; R_0805_2012Metric
R_BAL_1_12: 15.4k; R_0805_2012Metric
R_BAL_1_13: 52.3k; R_0805_2012Metric
R_BAL_1_14: 113k; R_0805_2012Metric
R_BAL_1_15: 61.9k; R_0805_2012Metric
Rb_N12: 750k; R_0805_2012Metric
Rb_N14: 200k; R_0805_2012Metric
Rf_N12, Rf_N13, Rf_N14, Rf_N15: 100k; R_0805_2012Metric
U1: TL074; SOIC-14_3.9x8.7mm_P1.27mm

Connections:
+5V_REF: J_STRADDLE_EDGE.B35, Rb_N12.1, Rb_N14.1
+15V: C_U1P.2, J_STRADDLE_EDGE.B33, J_STRADDLE_EDGE.B34, U1.4
-15V: C_U1N.1, J_STRADDLE_EDGE.B37, J_STRADDLE_EDGE.B38, U1.11
GND: C_U1N.2, C_U1P.1, H1.1, H2.1, J_STRADDLE_EDGE.A37, J_STRADDLE_EDGE.A38, R_BAL_1_12.2, R_BAL_1_13.2, R_BAL_1_14.2, R_BAL_1_15.2
INV_N12: R1_7_0.2, R1_8_0.2, R1_15_0.2, R1_22_0.2, R1_24_0.2, R1_25_0.2, R1_26_0.2, R1_27_0.2, R1_33_0.2, R1_34_0.2, R1_35_0.2, R1_36_0.2, R1_39_0.2, R1_40_0.2, R1_41_0.2, R1_42_0.2, R1_43_0.2, R1_44_0.2, R1_45_0.2, R1_48_0.2, R1_49_0.2, R1_50_0.2, R1_51_0.2, R1_52_0.2, R1_53_0.2, R1_54_0.2, R1_55_0.2, R1_57_0.2, R1_58_0.2, R1_59_0.2, R1_60_0.2, R1_61_0.2, R1_62_0.2, R1_63_0.2, Rb_N12.2, Rf_N12.1, U1.2
INV_N13: R1_8_1.2, R1_45_1.2, R1_52_1.2, R1_56_1.2, R1_62_1.2, R1_63_1.2, Rf_N13.1, U1.6
INV_N14: R1_1_2.2, R1_2_2.2, R1_3_2.2, R1_5_2.2, R1_6_2.2, R1_8_2.2, R1_9_2.2, R1_10_2.2, R1_11_2.2, R1_12_2.2, R1_13_2.2, R1_14_2.2, R1_15_2.2, R1_18_2.2, R1_20_2.2, R1_21_2.2, R1_24_2.2, R1_25_2.2, R1_26_2.2, R1_27_2.2, R1_28_2.2, R1_29_2.2, R1_32_2.2, R1_33_2.2, R1_34_2.2, R1_35_2.2, R1_36_2.2, R1_37_2.2, R1_38_2.2, R1_43_2.2, R1_44_2.2, R1_45_2.2, R1_56_2.2, R1_57_2.2, R1_58_2.2, R1_63_2.2, R_BAL_1_14.1, Rb_N14.2, Rf_N14.1, U1.9
INV_N15: R1_1_3.2, R1_8_3.2, R1_12_3.2, R1_50_3.2, Rf_N15.1, U1.13
IN_0: J_STRADDLE_EDGE.A1, R1_0_0.1, R1_0_2.1
IN_1: J_STRADDLE_EDGE.A2, R1_1_0.1, R1_1_2.1, R1_1_3.1
IN_2: J_STRADDLE_EDGE.A3, R1_2_0.1, R1_2_2.1
IN_3: J_STRADDLE_EDGE.A4, R1_3_0.1, R1_3_2.1
IN_4: J_STRADDLE_EDGE.A5, R1_4_0.1
IN_5: J_STRADDLE_EDGE.A6, R1_5_0.1, R1_5_2.1
IN_6: J_STRADDLE_EDGE.A7, R1_6_0.1, R1_6_2.1
IN_7: J_STRADDLE_EDGE.A8, R1_7_0.1
IN_8: J_STRADDLE_EDGE.A9, R1_8_0.1, R1_8_1.1, R1_8_2.1, R1_8_3.1
IN_9: J_STRADDLE_EDGE.A10, R1_9_0.1, R1_9_2.1
IN_10: J_STRADDLE_EDGE.A11, R1_10_0.1, R1_10_2.1
IN_11: J_STRADDLE_EDGE.A12, R1_11_0.1, R1_11_2.1
IN_12: J_STRADDLE_EDGE.A13, R1_12_0.1, R1_12_1.1, R1_12_2.1, R1_12_3.1
IN_13: J_STRADDLE_EDGE.A14, R1_13_0.1, R1_13_2.1
IN_14: J_STRADDLE_EDGE.A15, R1_14_0.1, R1_14_2.1
IN_15: J_STRADDLE_EDGE.A16, R1_15_0.1, R1_15_2.1
IN_16: J_STRADDLE_EDGE.A17, R1_16_0.1, R1_16_2.1
IN_17: J_STRADDLE_EDGE.A18, R1_17_0.1, R1_17_2.1
IN_18: J_STRADDLE_EDGE.A19, R1_18_0.1, R1_18_2.1
IN_19: J_STRADDLE_EDGE.A20, R1_19_0.1
IN_20: J_STRADDLE_EDGE.A21, R1_20_0.1, R1_20_2.1
IN_21: J_STRADDLE_EDGE.A22, R1_21_2.1
IN_22: J_STRADDLE_EDGE.A23, R1_22_0.1
IN_23: J_STRADDLE_EDGE.A24, R1_23_0.1, R1_23_2.1
IN_24: J_STRADDLE_EDGE.A25, R1_24_0.1, R1_24_2.1
IN_25: J_STRADDLE_EDGE.A26, R1_25_0.1, R1_25_2.1
IN_26: J_STRADDLE_EDGE.A27, R1_26_0.1, R1_26_2.1
IN_27: J_STRADDLE_EDGE.A28, R1_27_0.1, R1_27_2.1
IN_28: J_STRADDLE_EDGE.A29, R1_28_0.1, R1_28_2.1
IN_29: J_STRADDLE_EDGE.A30, R1_29_0.1, R1_29_2.1
IN_31: J_STRADDLE_EDGE.A32, R1_31_0.1, R1_31_2.1
IN_32: J_STRADDLE_EDGE.B1, R1_32_0.1, R1_32_2.1
IN_33: J_STRADDLE_EDGE.B2, R1_33_0.1, R1_33_2.1
IN_34: J_STRADDLE_EDGE.B3, R1_34_0.1, R1_34_2.1
IN_35: J_STRADDLE_EDGE.B4, R1_35_0.1, R1_35_1.1, R1_35_2.1
IN_36: J_STRADDLE_EDGE.B5, R1_36_0.1, R1_36_2.1, R1_36_3.1
IN_37: J_STRADDLE_EDGE.B6, R1_37_0.1, R1_37_2.1
IN_38: J_STRADDLE_EDGE.B7, R1_38_0.1, R1_38_2.1
IN_39: J_STRADDLE_EDGE.B8, R1_39_0.1, R1_39_2.1
IN_40: J_STRADDLE_EDGE.B9, R1_40_0.1, R1_40_2.1
IN_41: J_STRADDLE_EDGE.B10, R1_41_0.1, R1_41_2.1
IN_42: J_STRADDLE_EDGE.B11, R1_42_0.1, R1_42_2.1
IN_43: J_STRADDLE_EDGE.B12, R1_43_0.1, R1_43_2.1
IN_44: J_STRADDLE_EDGE.B13, R1_44_0.1, R1_44_2.1
IN_45: J_STRADDLE_EDGE.B14, R1_45_0.1, R1_45_1.1, R1_45_2.1
IN_47: J_STRADDLE_EDGE.B16, R1_47_0.1, R1_47_2.1
IN_48: J_STRADDLE_EDGE.B17, R1_48_0.1, R1_48_2.1
IN_49: J_STRADDLE_EDGE.B18, R1_49_0.1, R1_49_2.1
IN_50: J_STRADDLE_EDGE.B19, R1_50_0.1, R1_50_2.1, R1_50_3.1
IN_51: J_STRADDLE_EDGE.B20, R1_51_0.1, R1_51_2.1
IN_52: J_STRADDLE_EDGE.B21, R1_52_0.1, R1_52_1.1, R1_52_2.1, R1_52_3.1
IN_53: J_STRADDLE_EDGE.B22, R1_53_0.1, R1_53_2.1
IN_54: J_STRADDLE_EDGE.B23, R1_54_0.1, R1_54_2.1
IN_55: J_STRADDLE_EDGE.B24, R1_55_0.1, R1_55_2.1
IN_56: J_STRADDLE_EDGE.B25, R1_56_1.1, R1_56_2.1
IN_57: J_STRADDLE_EDGE.B26, R1_57_0.1, R1_57_2.1
IN_58: J_STRADDLE_EDGE.B27, R1_58_0.1, R1_58_2.1
IN_59: J_STRADDLE_EDGE.B28, R1_59_0.1, R1_59_1.1
IN_60: J_STRADDLE_EDGE.B29, R1_60_0.1, R1_60_2.1
IN_61: J_STRADDLE_EDGE.B30, R1_61_0.1
IN_62: J_STRADDLE_EDGE.B31, R1_62_0.1, R1_62_1.1, R1_62_2.1
IN_63: J_STRADDLE_EDGE.B32, R1_63_0.1, R1_63_1.1, R1_63_2.1
POS_N12: R1_0_0.2, R1_1_0.2, R1_2_0.2, R1_3_0.2, R1_4_0.2, R1_5_0.2, R1_6_0.2, R1_9_0.2, R1_10_0.2, R1_11_0.2, R1_12_0.2, R1_13_0.2, R1_14_0.2, R1_16_0.2, R1_17_0.2, R1_18_0.2, R1_19_0.2, R1_20_0.2, R1_23_0.2, R1_28_0.2, R1_29_0.2, R1_31_0.2, R1_32_0.2, R1_37_0.2, R1_38_0.2, R1_47_0.2, R_BAL_1_12.1, U1.3
POS_N13: R1_12_1.2, R1_35_1.2, R1_59_1.2, R_BAL_1_13.1, U1.5
POS_N14: R1_0_2.2, R1_16_2.2, R1_17_2.2, R1_23_2.2, R1_31_2.2, R1_39_2.2, R1_40_2.2, R1_41_2.2, R1_42_2.2, R1_47_2.2, R1_48_2.2, R1_49_2.2, R1_50_2.2, R1_51_2.2, R1_52_2.2, R1_53_2.2, R1_54_2.2, R1_55_2.2, R1_60_2.2, R1_62_2.2, U1.10
POS_N15: R1_36_3.2, R1_52_3.2, R_BAL_1_15.1, U1.12
V_SUM_12: J_STRADDLE_EDGE.A33, Rf_N12.2, U1.1
V_SUM_13: J_STRADDLE_EDGE.A34, Rf_N13.2, U1.7
V_SUM_14: J_STRADDLE_EDGE.A35, Rf_N14.2, U1.8
V_SUM_15: J_STRADDLE_EDGE.A36, Rf_N15.2, U1.14
